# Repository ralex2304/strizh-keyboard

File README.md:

# [WIP] Strizh keyboard

**Strizh** (Russian for "swift") is an ultra low profile 44-48 key split with Kailh PG1316S switches

## Planned features

- ~9 mm thickness

- ZMK firmware

- NRF52840 SuperMini controllers

- optional 40 mm Cirque trackpad

- optional nice!view display

## PCB Draft

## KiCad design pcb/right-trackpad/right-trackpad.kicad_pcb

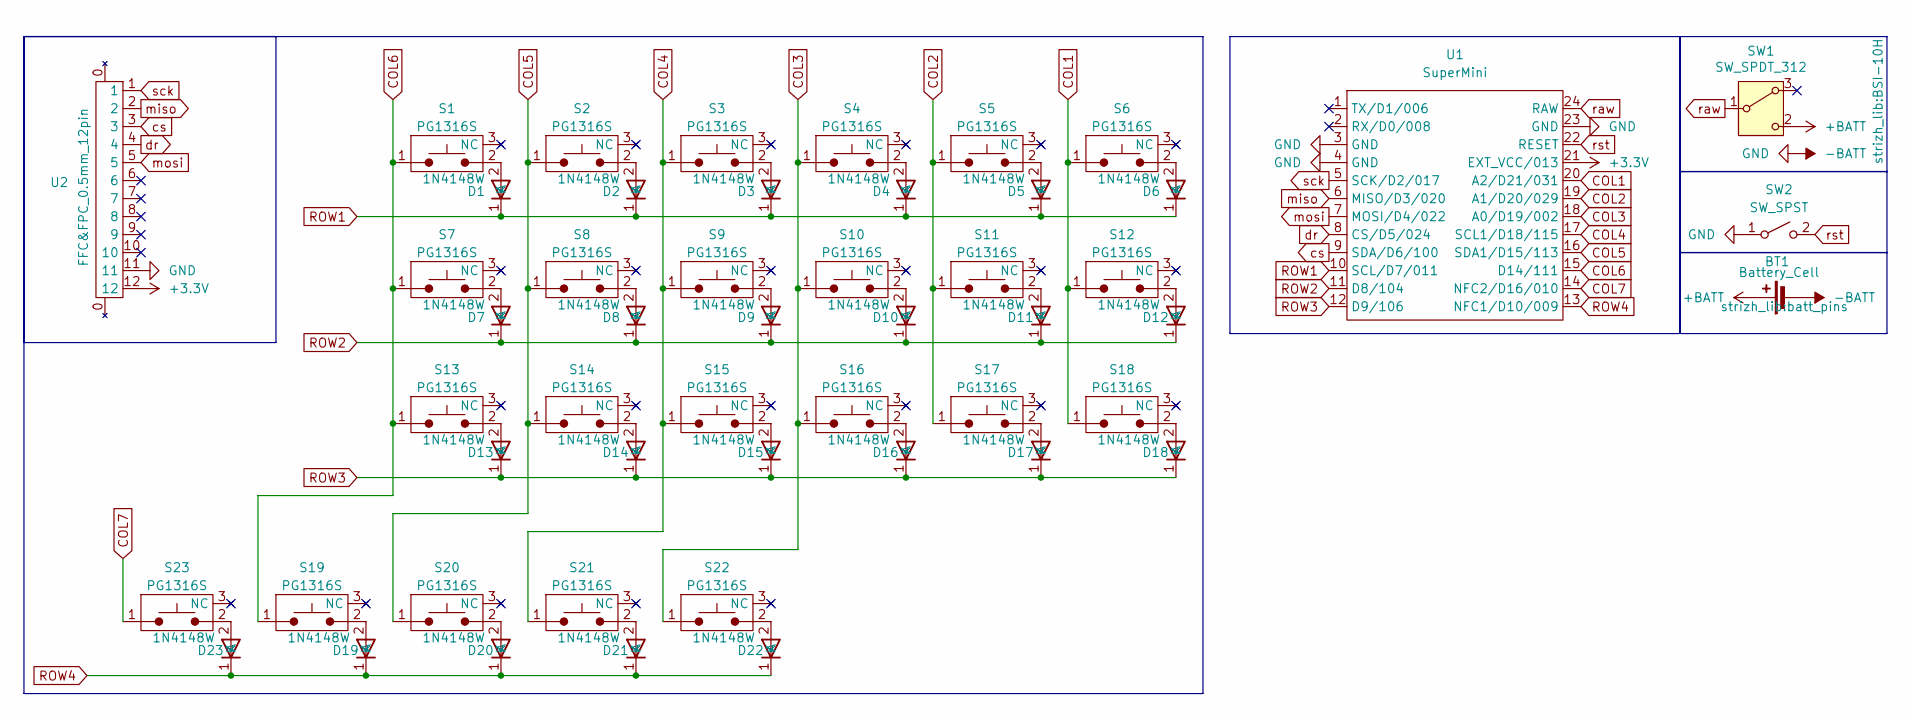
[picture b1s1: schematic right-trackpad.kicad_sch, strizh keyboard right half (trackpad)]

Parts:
BT1: Battery_Cell; batt_pins
D1, D2, D3, D4, D5, D6, D7, D8, D9, D10, D11, D12, D13, D14, D15, D16, D17, D18, D19, D20, D21, D22, D23: 1N4148W; 1N4148W_SOD-123
S1, S2, S3, S4, S5, S6, S7, S8, S9, S10, S11, S12, S13, S14, S15, S16, S17, S18, S19, S20, S21, S22, S23: PG1316S
SW1: SW_SPDT_312; BSI-10H
SW2: SW_SPST; SW_SPST_SKQG_WithStem
U1: SuperMini; supermini_nrf52840
U2: FFC&FPC_0.5mm_12pin

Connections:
+3.3V: U1.21 (EXT_VCC/013), U2.12
+BATT: BT1.1 (+), SW1.2 (C)
-BATT: BT1.2 (-), SW2.1 (A), U1.3 (GND), U1.4 (GND), U1.23 (GND), U2.11
COL1: S6.1, S12.1, S18.1, U1.20 (A2/D21/031)
COL2: S5.1, S11.1, S17.1, U1.19 (A1/D20/029)
COL3: S4.1, S10.1, S16.1, S22.1, U1.18 (A0/D19/002)
COL4: S3.1, S9.1, S15.1, S21.1, U1.17 (SCL1/D18/115)
COL5: S2.1, S8.1, S14.1, S20.1, U1.16 (SDA1/D15/113)
COL6: S1.1, S7.1, S13.1, S19.1, U1.15 (D14/111)
COL7: S23.1, U1.14 (NFC2/D16/010)
unnamed: D1.2 (A), S1.2
unnamed: D2.2 (A), S2.2
unnamed: D3.2 (A), S3.2
unnamed: D4.2 (A), S4.2
unnamed: D5.2 (A), S5.2
unnamed: D6.2 (A), S6.2
unnamed: D7.2 (A), S7.2
unnamed: D8.2 (A), S8.2
unnamed: D9.2 (A), S9.2
unnamed: D10.2 (A), S10.2
unnamed: D11.2 (A), S11.2
unnamed: D12.2 (A), S12.2
unnamed: D13.2 (A), S13.2
unnamed: D14.2 (A), S14.2
unnamed: D15.2 (A), S15.2
unnamed: D16.2 (A), S16.2
unnamed: D17.2 (A), S17.2
unnamed: D18.2 (A), S18.2
unnamed: D19.2 (A), S19.2
unnamed: D20.2 (A), S20.2
unnamed: D21.2 (A), S21.2
unnamed: D22.2 (A), S22.2
unnamed: D23.2 (A), S23.2
ROW1: D1.1 (K), D2.1 (K), D3.1 (K), D4.1 (K), D5.1 (K), D6.1 (K), U1.10 (SCL/D7/011)
ROW2: D7.1 (K), D8.1 (K), D9.1 (K), D10.1 (K), D11.1 (K), D12.1 (K), U1.11 (D8/104)
ROW3: D13.1 (K), D14.1 (K), D15.1 (K), D16.1 (K), D17.1 (K), D18.1 (K), U1.12 (D9/106)
ROW4: D19.1 (K), D20.1 (K), D21.1 (K), D22.1 (K), D23.1 (K), U1.13 (NFC1/D10/009)
cs: U1.9 (SDA/D6/100), U2.3
dr: U1.8 (CS/D5/024), U2.4
miso: U1.6 (MISO/D3/020), U2.2
mosi: U1.7 (MOSI/D4/022), U2.5
raw: SW1.1 (B), U1.24 (RAW)
rst: SW2.2 (B), U1.22 (RESET)
sck: U1.5 (SCK/D2/017), U2.1

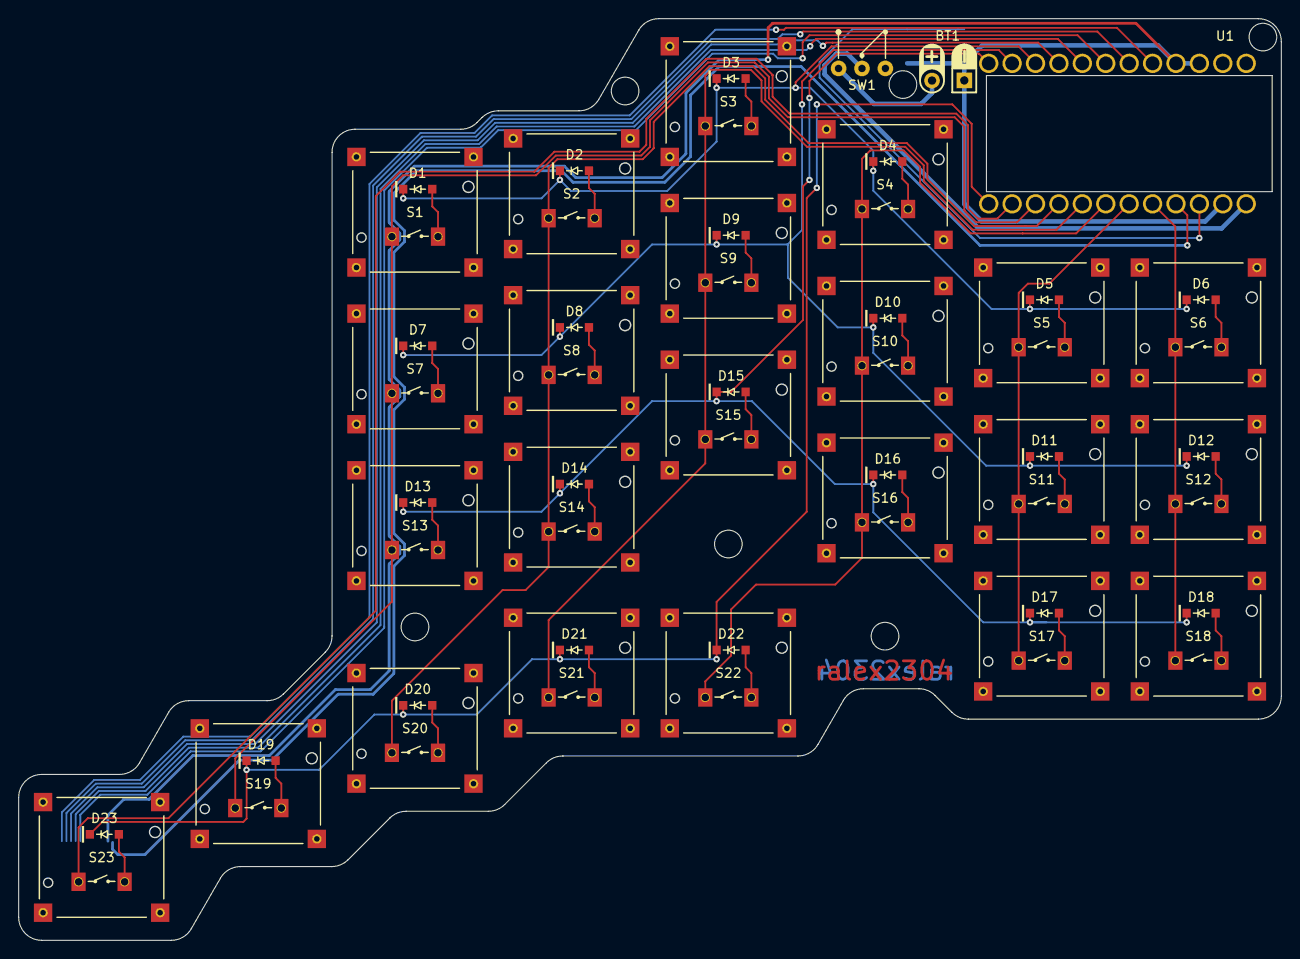
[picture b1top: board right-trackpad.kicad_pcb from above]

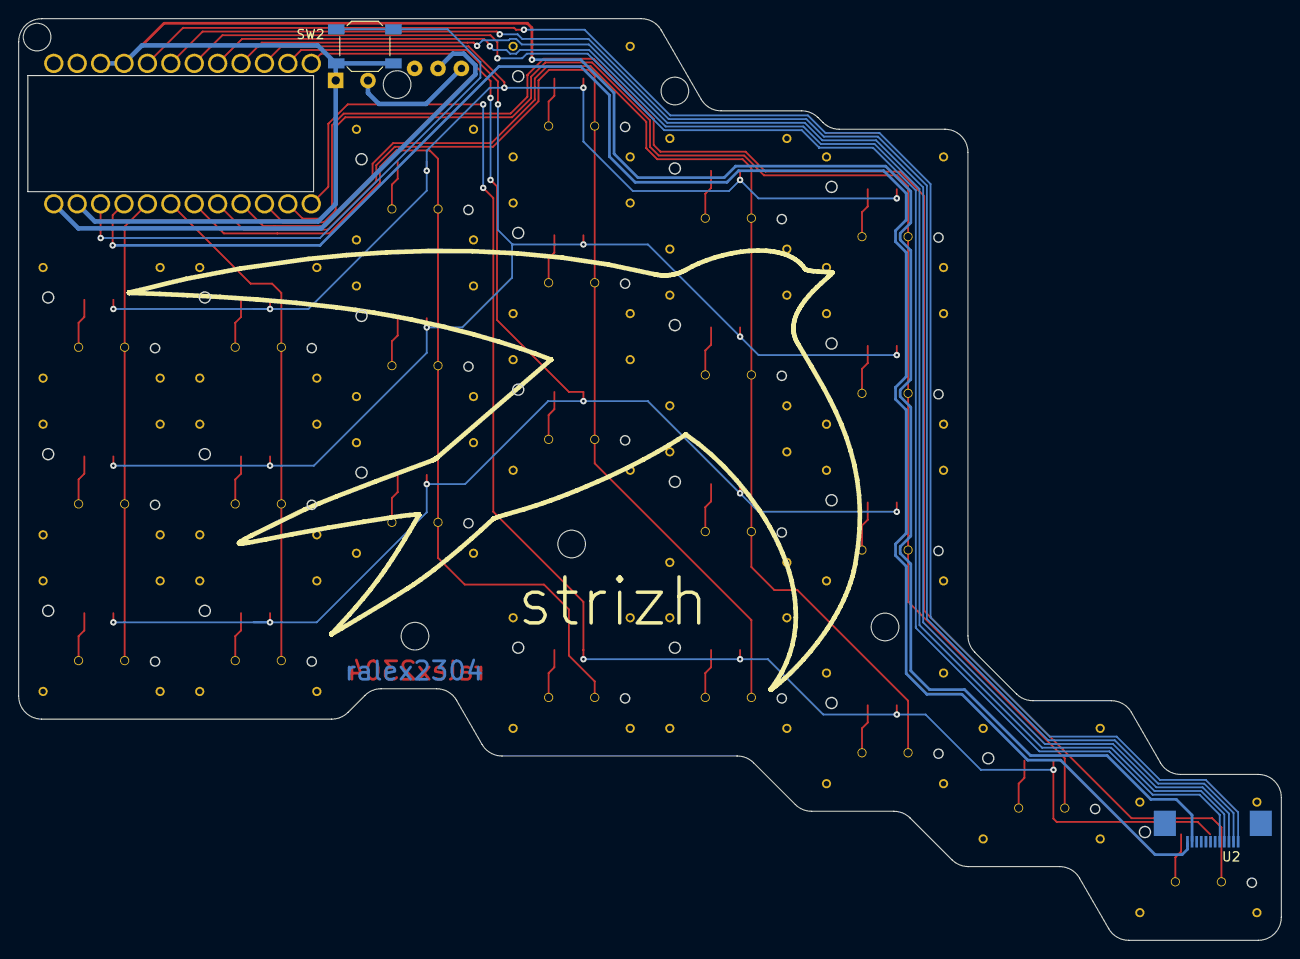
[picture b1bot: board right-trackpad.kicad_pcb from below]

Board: 2 copper layers, 136.9 x 99.9 mm, 51 parts (2 on the bottom side), 44 nets.

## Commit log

2025-06-30 Add right half pcb draft
2025-06-30 Add readme
2025-07-01 Add left half pcb draft
2025-07-13 Change horizontal spacing and add nice!view to left half
2025-07-20 Add vias to switch footprints
2026-01-26 Fix pin naming of supermini
2026-02-18 Fix slight shift, enlarge vias to meet manufacturing requirements
2026-02-23 Init left7col case
2026-02-23 Add power switch chamfer
2026-02-24 Add right trackpad case
2026-02-28 Minor fixes after first draft print
2026-03-01 Decrease top fillets, increase screw chamfers
2026-03-03 Rework front part, create top-bottom coupling
2026-03-08 Add latches
2026-06-10 Final version
2026-06-10 Dongle case
2026-06-10 Dongle minimal angled stand
